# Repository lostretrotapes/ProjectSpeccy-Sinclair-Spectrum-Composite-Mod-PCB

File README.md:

# ProjectSpeccy-Sinclair-Spectrum-Composite-Mod-PCB

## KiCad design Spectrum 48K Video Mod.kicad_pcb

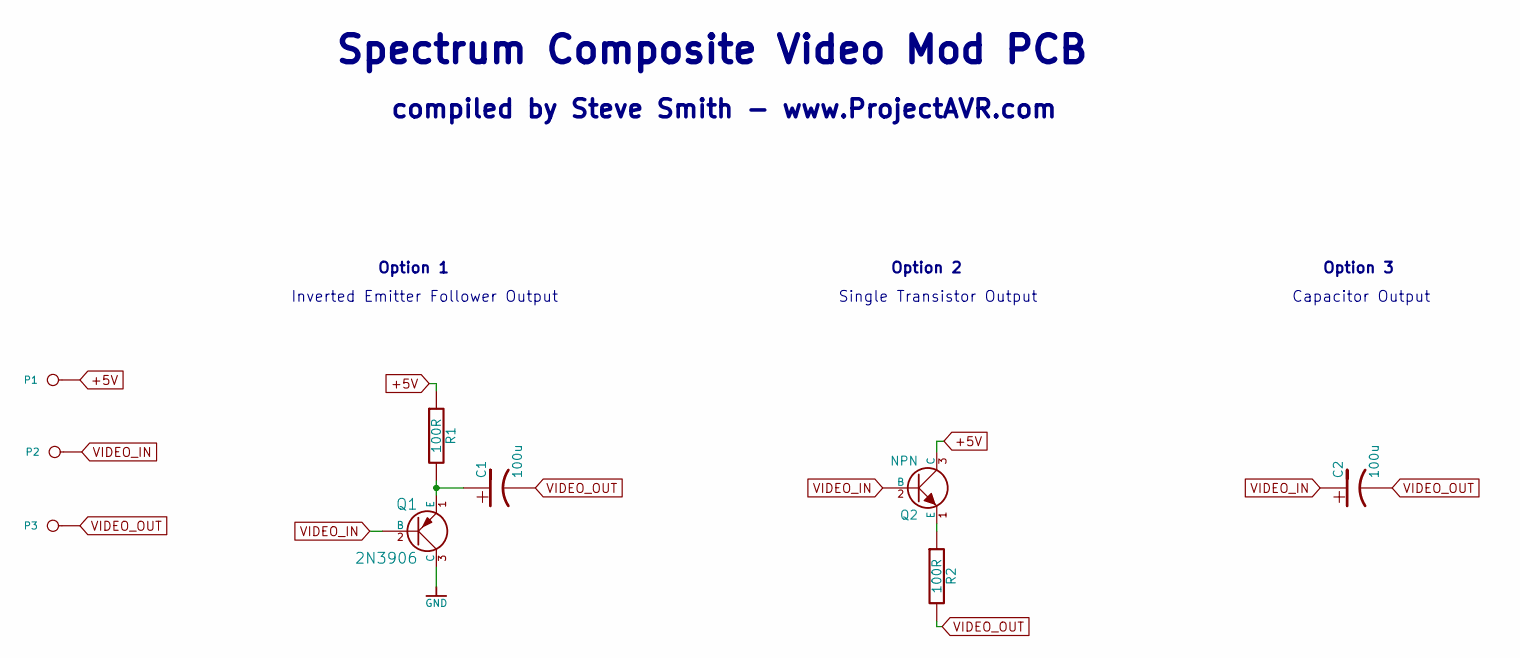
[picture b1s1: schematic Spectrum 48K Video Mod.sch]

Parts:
C1, C2: 100u; CP_Radial_D7.5mm_P2.50mm
P1, P2, P3: CONN_1; Pin_Header_Straight_1x01_Pitch2.54mm
Q1: 2N3906; TO-92_Inline_Narrow_Oval
Q2: NPN; TO-92_Inline_Narrow_Oval
R1, R2: 100R; R_Axial_DIN0207_L6.3mm_D2.5mm_P10.16mm_Horizontal

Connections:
+5V: P1.1, Q2.3 (C), R1.1
GNDPWR: Q1.3 (C)
unnamed: C1.1, Q1.1 (E), R1.2
unnamed: Q2.1 (E), R2.1
VIDEO_IN: C2.1, P2.1, Q1.2 (B), Q2.2 (B)
VIDEO_OUT: C1.2, C2.2, P3.1, R2.2

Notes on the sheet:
Option 1
Inverted Emitter Follower Output
Option 3
Capacitor Output
Spectrum Composite Video Mod PCB
Option 2
Single Transistor Output
compiled by Steve Smith - www.ProjectAVR.com

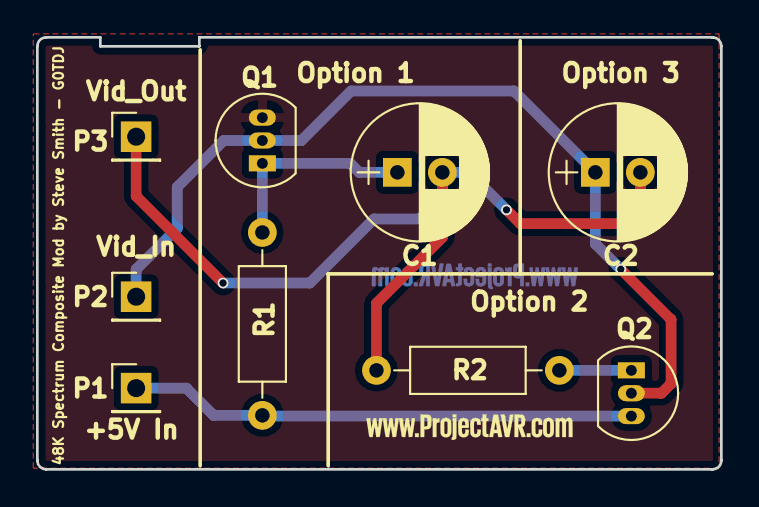
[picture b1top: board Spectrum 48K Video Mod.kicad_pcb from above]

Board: 2 copper layers, 38.0 x 24.0 mm, 9 parts (0 on the bottom side), 5 nets.
